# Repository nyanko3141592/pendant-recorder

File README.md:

# pendant-recorder

DTP401525-XE（3.7V・110mAh）を使う、連続録音型のUSB-Cネックレスレコーダーです。現行の4層設計レビューは[確認パッケージ](hardware/xe-minimal/preorder-20261029/release-review-20261029-aligned/START-HERE.txt)に集約しています。現成果物の入口は[初号試作設計](hardware/xe-minimal/preorder-20261029/release-review-20261029-aligned/first-prototype/README.md)です。配線bay・接着ポケット付きケースと同版キットを追加し、C30を同定格在庫品へ変更しました。ファームの購入者向け書込み版と物理性能は未確定です。

**現状は `HOLD` です。注文、支払い、製造データのアップロードは禁止です。** CAD・静的検査・ソフトウェア試験は通過していますが、安全性、16時間連続録音、30時間保存、3 OSでのUSB取込み、ケース強度は実機未確認です。

## 優先順位

今回は低コストで小型の初号試作を作り、実際に使って評価します。基本安全対策を前提に、**使い勝手（特に電池持ち）→小型化→初回費用**の順で判断します。性能は根拠のある理論見積りで達成を見込めれば試作判断へ進め、実測や量産認定を事前条件にしません。室温の明示した仮定では平均3.86mA・約19.9時間（使用可能77mAh）となりますが、SPI電流・動作時間・使用可能容量は未実測です。詳細は[現行要件](docs/requirements.md)を正本とします。

## 現行候補

基板27.5mm角・最大4層・通常through via・固定DTP401525-XE・16時間録音・30時間以上保存が現要件です。旧6層正本とCase V5は履歴として保全し、現候補の製造入力には使用しません。

| 項目 | 現在の確認先 | 判定 |
| --- | --- | --- |
| 回路・4層基板 | [同版KiCad設計](hardware/xe-minimal/preorder-20261029/release-review-20261029-aligned/design/) | 基準PCB b3cdfc064b43…、DRC/未接続/parity 0。電気性能の認定ではない |
| BOM・調達 | [全BOM確認](hardware/xe-minimal/preorder-20261029/release-review-20261029-aligned/live-full-bom-summary.json) | 68実装・36型番。U1/U12/J1通常Pre-order。C30は同定格C501830へ変更し公開実装可能45,731個を確認 |
| 製造資料 | [確認パッケージ](hardware/xe-minimal/preorder-20261029/release-review-20261029-aligned/START-HERE.txt) | Gerber/drill/BOM/CPL同梱。回転・DFM・90Ω・総額は未確定、upload禁止 |
| ケース・実寸ダミー | [現優先候補](hardware/xe-minimal/preorder-20261029/release-review-20261029-aligned/mechanical-first-prototype/ASSEMBLY.md) | 約30.8×37.5×14.2mm。配線通路・蓋接着ポケット、ケース3点＋PCBA/電池ダミーSTEP/STL/3MF。CADとoffline slice確認、現物fit・強度は未認定 |
| ファーム・取込み | [STM32](firmware/stm32/) / [host](host/README.md) | 現codecで暗号化・復号の非実機試験済み。工場imageと3 OS実機動作は未確定 |
| 組立・試験 | [現4層の手順](hardware/xe-minimal/preorder-20261029/release-review-20261029-aligned/ASSEMBLY-AND-EVT.txt) | 発注前の設計確認と試作後の実測を分離。実測合格は主張しない |
| 残件 | [release-gates.json](hardware/xe-minimal/preorder-20261029/release-review-20261029-aligned/release-gates.json) | 部品入庫・注文時DFM/placement・正式USB ID/cutoff/工場format・実物fit/安全/性能評価が残る |

## 製造と購入者作業の境界

JLCPCB Standard PCBAで両面実装、検査、書込み、出荷前パネル分割まで完結させる方針です。購入者による電子部品の調達、部品支給、はんだ、圧着、配線加工は認めません。購入者が用意して組み付けるものは、固定型番のDTP401525-XE、ケース、ネックレス紐だけです。業者完結できない場合は代替部品または設計変更とし、個別問い合わせを前提に進めません。

## 発注を止めている条件

発注前の設計残件は[release-gates.json](hardware/xe-minimal/preorder-20261029/release-review-20261029-aligned/release-gates.json)を参照してください。試作後の安全・16時間録音・30時間保存・USB・ケース強度試験は未実施です。発注前設計確認の完了と実機認定を区別し、注文・支払い・upload・業者連絡・実印刷は禁止のままです。

旧XIAO/ESP32、旧PCB、旧ケース、外付け温度センサー案は比較・履歴資料であり、現行製造データへ混ぜません。

[プロトコル](docs/protocol/README.md) / [貢献手順](CONTRIBUTING.md) / [MITライセンス](LICENSE) / [第三者通知](THIRD_PARTY_NOTICES.md)

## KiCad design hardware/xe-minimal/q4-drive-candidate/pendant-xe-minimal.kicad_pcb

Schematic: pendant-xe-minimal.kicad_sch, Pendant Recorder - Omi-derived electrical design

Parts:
C1, C2, C3, C6, C9, C22, C26: 100n; C_0402_1005Metric
C4: 10u; C_0603_1608Metric
C5: 4.7u; C_0603_1608Metric
C7, C16, C25: 1u; C_0402_1005Metric
C13: 2.2u 10V; C_0402_1005Metric
C14: 2.2u; C_0402_1005Metric
C15: 10u 10V effective >=1u; C_0603_1608Metric
C27: 4.7u effective TBD; C_0603_1608Metric
C28: 10n; C_0402_1005Metric
C29, C32, C33: 100n 10V; C_0402_1005Metric
C30: 50p 50V C0G; C_0402_1005Metric
C31: 1u 10V; C_0402_1005Metric
D6: amber LED 0402 TBD; LED_0402_1005Metric
J1: USB4105-GF-A (candidate); USB_C_GCT_USB4105_GroundLand112
J2: Molex781710003 / DTP401525-XE; Molex_Pico-EZmate_78171-0003_1x03-1MP_P1.20mm_Vertical
J3: Factory SWD pogo candidate; SWD_Pogo_5Pad_P1.27mm
Q3, Q4: DMN63D8L-7; SOT-23
Q5, Q6, Q7: 2N7002; SOT-23
R1: 0R; R_0402_1005Metric
R2: 10k; R_0402_1005Metric
R3, R4, R13, R15, R22: 100k; R_0402_1005Metric
R6, R7: 5.1k 1%; R_0402_1005Metric
R10: 6.8k 1%; R_0402_1005Metric
R11, R39: 20k 1%; R_0402_1005Metric
R12, R36, R37, R38, R40, R45, R46, R49, R50: 100k 1%; R_0402_1005Metric
R14: 1M; R_0402_1005Metric
R21, R23: 22R tentative; R_0402_1005Metric
R24, R25, R28: 47k; R_0402_1005Metric
R32: 6.8k tentative; R_0402_1005Metric
R33, R34: 1M 1%; R_0402_1005Metric
R35, R47, R48: 10k 1%; R_0402_1005Metric
R41: 7.5k 1%; R_0402_1005Metric
R42: 130k 1%; R_0402_1005Metric
R43: 4.7k 1%; R_0402_1005Metric
R44: 390k 1%; R_0402_1005Metric
SW1: B3U-1000P (candidate); SW_SPST_B3U-1000P
TH1: NCP18XH103F03RB 10k 1% B3380 candidate; R_0603_1608Metric
TP1, TP2, TP3, TP5, TP6: TestPoint; TestPoint_Pad_D1.0mm
U1: STM32U535CEU6; QFN-48-1EP_7x7mm_P0.5mm_EP5.6x5.6mm
U2: USBLC6-2P6; SOT-666
U3: BQ25185DLHR; Texas_DLH0010A_WSON-10-1EP_2.2x2mm_P0.4mm_EP0.9x1.5mm
U4: TPS7A0233PDBVR; SOT-23-5
U8: IM69D130V01XTSA1; IM69D130_JLC_SMD_trial
U10: TPS22916CYFPR; TPS22916_YFP4
U11: CSNP32GCR01-BOW candidate; CSNP32GCR01_LGA8
U12: TLV7042DDFR; SOT-23-8
U13: MAX4995CAUT+T; SOT-23-6
U14: SN74HCS74DYYR; Texas_DYY0014A
U15: TLV803EB29DBZR; SOT-23

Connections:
/BAT: C14.1, J2.1 (PACK_PLUS), R33.1, TP1.1, U3.2 (BAT)
/BAT_ADC: C28.1, R33.2, R34.1, U1.11 (PA1)
/BAT_TS: R37.2, TH1.1 (SENSE), U12.2 (INA-), U12.5 (INB+)
/BOOT0: R3.1, U1.44 (PH3)
/BUTTON_N: R4.2, SW1.1, U1.38 (PA15)
/CC1: J1.A5 (CC1), R6.1
/CC2: J1.B5 (CC2), R7.1
/CHARGER_TS: R35.1, U3.6 (TS_MR)
/CHG_ALLOW: R43.1, U1.20 (PB2)
/CHG_GUARD_GATE: Q4.1 (G), R36.1, R43.2, U12.1 (OUTA), U12.7 (OUTB)
/CHG_INHIBIT_GATE: Q4.3 (D), R12.2, U3.4 (CE_N)
/CHG_N: R11.2, U1.27 (PB14), U3.9 (STAT1)
/GND: C1.2, C2.2, C3.2, C4.2, C5.2, C6.2, C7.2, C9.2, C13.2, C14.2, C15.2, C16.2, C22.2, C25.2, C26.2, C27.2, C28.2, C29.2, C30.2, C31.2, C32.2, C33.2, D6.1 (K), J1.A1 (GND), J1.A12 (GND), J1.B1 (GND), J1.B12 (GND), J1.SH (SHIELD), J2.3 (PACK_MINUS), J3.5 (GND), Q3.2 (S), Q4.2 (S), Q5.2 (S), Q6.2 (S), Q7.2 (S), R3.2, R6.2, R7.2, R10.2, R14.2, R22.2, R34.2, R35.2, R36.2, R39.2, R41.2, R42.2, R44.2, R46.2, R49.2, R50.2, SW1.2, TH1.2 (RETURN), TP6.1, U1.8 (VSSA), U1.23 (VSS), U1.35 (VSS), U1.47 (VSS), U1.49 (VSS), U2.2 (GND), U3.5 (GND), U3.11 (EP), U4.2 (GND), U8.4 (SELECT), U8.5 (GND), U10.B1 (GND), U11.4 (VSS), U12.4 (VEE), U13.2 (GND), U14.7 (GND), U14.11 (2CLK), U14.12 (2D), U14.13 (2CLR_N), U15.1 (GND)
/ILIM_VSET: R42.1, U3.7 (ILIM_VSET)
/ISET: C30.1, R10.1, U3.8 (ISET)
/NRST: C9.1, J3.3 (nRESET), R2.2, U1.7 (NRST)
/PDM_CLK: R21.2, U8.3 (CLOCK)
/PDM_CLK_MCU: R21.1, U1.39 (PB3)
/PDM_DATA: U1.40 (PB4), U8.1 (DATA)
/SD_CLK: R23.2, U11.3 (CLK)
/SD_CLK_MCU: R23.1, U1.15 (PA5)
/SD_CS_N: R28.2, U1.14 (PA4), U11.2 (CS_N)
/SD_EN: R22.1, U1.41 (PB5), U10.B2 (ON)
/SD_MISO: R25.2, U1.16 (PA6), U11.6 (DO)
/SD_MOSI: R24.2, U1.17 (PA7), U11.5 (DI)
/SD_V3: C26.1, C27.1, R24.1, R25.1, R28.1, TP5.1, U10.A1 (VOUT), U11.8 (VDD)
/STATUS_LED: R32.1, U1.29 (PA8)
/STATUS_LED_A: D6.2 (A), R32.2
/SWCLK: J3.4 (SWCLK), U1.37 (PA14)
/SWDIO: J3.2 (SWDIO), U1.34 (PA13)
/SYS: C15.1, TP2.1, U3.1 (SYS), U4.1 (IN), U4.3 (EN)
/TS_COLD_REF: R38.2, R39.1, U12.3 (INA+)
/TS_HOT_REF: R40.2, R41.1, U12.6 (INB-)
/USB_DM: J1.A7 (D-), J1.B7 (D-), U1.32 (PA11), U2.3 (IO2), U2.4 (IO2)
/USB_DP: J1.A6 (D+), J1.B6 (D+), U1.33 (PA12), U2.1 (IO1), U2.6 (IO1)
/USB_HIGH_BUDGET: Q5.1 (G), R46.1, U1.42 (PB6)
/USB_HIGH_BUDGET_DRAIN: Q5.3 (D), R45.2
/USB_ILIM_SET: R44.1, R45.1, U13.3 (SETI)
/USB_INPUT_ON: U13.4 (ON), U14.6 (1Q_N)
/USB_LATCH_CLEAR_N: Q7.3 (D), R48.2, U14.1 (1CLR_N), U15.2 (RESET_N)
/USB_LATCH_CLOCK: Q6.3 (D), R47.2, U14.3 (1CLK)
/USB_RESUME_PULSE: Q7.1 (G), R50.1, U1.19 (PB1)
/USB_SUSPEND_PULSE: Q6.1 (G), R49.1, U1.12 (PA2)
/V3V3: C1.1, C2.1, C3.1, C4.1, C16.1, C22.1, C25.1, C29.1, J3.1 (VTref), R1.1, R2.1, R4.1, R11.1, R15.1, R37.1, R38.1, R40.1, TP3.1, U1.1 (VBAT), U1.24 (VDD), U1.36 (VDD), U1.48 (VDD), U4.5 (OUT), U8.2 (VDD), U10.A2 (VIN), U12.8 (VCC)
/VBUS: C31.1, C32.1, C33.1, J1.A4 (VBUS), J1.A9 (VBUS), J1.B4 (VBUS), J1.B9 (VBUS), R13.1, R47.1, R48.1, U2.5 (VBUS), U13.5 (IN), U14.2 (1D), U14.4 (1PRE_N), U14.10 (2PRE_N), U14.14 (VCC), U15.3 (VDD)
/VBUS_GATE: Q3.1 (G), R13.2, R14.1
/VBUS_LIMITED: C13.1, R12.1, U3.10 (IN), U13.1 (OUT)
/VBUS_N: Q3.3 (D), R15.2, U1.10 (PA0)
/VCAP: C5.1, U1.22 (VCAP)
/VDDA: C6.1, C7.1, R1.2, U1.9 (VDDA)

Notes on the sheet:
01 MCU / RTC / UI
02 USB-C / CHARGER
03 POWER / FUEL GAUGE
04 AUDIO / SD / INDICATORS
ENGINEERING DRAFT - NOT FOR FABRICATION - See hardware/xe-minimal/README.md

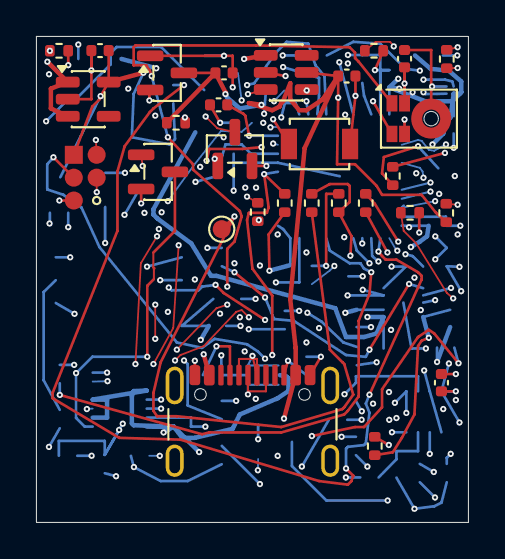
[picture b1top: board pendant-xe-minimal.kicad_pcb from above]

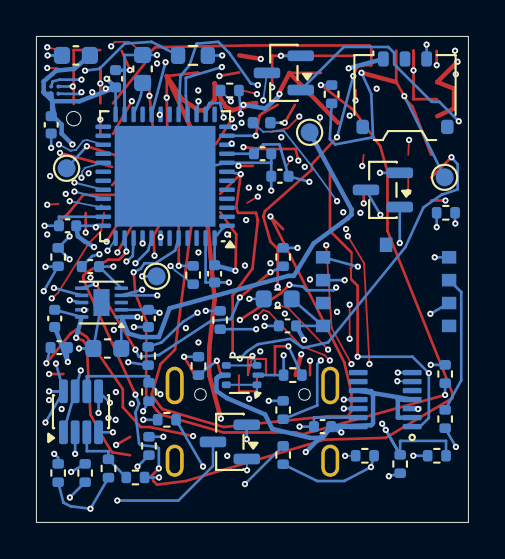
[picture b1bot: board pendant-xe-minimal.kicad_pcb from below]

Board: 6 copper layers, 24.0 x 27.0 mm, 86 parts (57 on the bottom side), 50 nets.

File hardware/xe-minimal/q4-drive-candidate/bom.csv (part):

Reference,Part/value,Footprint,Design note
U1,STM32U535CEU6,Package_DFN_QFN:QFN-48-1EP_7x7mm_P0.5mm_EP5.6x5.6mm,512KB Flash/274KB RAM; non-SMPS UFQFPN48. PB3/PB4 ADF AF3; PA5/6/7 SPI1 AF5. VDD USB shared 3.3V. JLC acceptance and pin review pending.
C1,100n,Capacitor_SMD:C_0402_1005Metric,
C4,10u,Capacitor_SMD:C_0603_1608Metric,Main bulk capacitor; check startup and effective capacitance.
C9,100n,Capacitor_SMD:C_0402_1005Metric,
R2,10k,Resistor_SMD:R_0402_1005Metric,
J3,Factory SWD pogo candidate,PendantMinimal:SWD_Pogo_5Pad_P1.27mm,Five exposed pads; factory fixture required; VTref sense only. No buyer flashing.
SW1,B3U-1000P (candidate),Button_Switch_SMD:SW_SPST_B3U-1000P,
R4,100k,Resistor_SMD:R_0402_1005Metric,
J1,USB4105-GF-A (candidate),PendantD1:USB_C_GCT_USB4105_GroundLand112,Exact footprint and shield pad numbering pending connector selection
R6,5.1k 1%,Resistor_SMD:R_0402_1005Metric,
R7,5.1k 1%,Resistor_SMD:R_0402_1005Metric,
U2,USBLC6-2P6,Package_TO_SOT_SMD:SOT-666,"ST DS4260 same 6-pin function diagram; smaller package, LCSC C15999 catalog; orientation/land pattern final audit pending."
C13,2.2u 10V,Capacitor_SMD:C_0402_1005Metric,
U3,BQ25185DLHR,Package_DFN_QFN:Texas_DLH0010A_WSON-10-1EP_2.2x2mm_P0.4mm_EP0.9x1.5mm,XE candidate4.1V ±0.5% =>4.1205V upper;44.12mA nominal charging. ILIM500 requires host power policy; thermal contact and battery capacity at4.1V unqualified; charge inhibited.
R10,6.8k 1%,Resistor_SMD:R_0402_1005Metric,XE prototype44.12mA nominal;10%IC/1%R screen39.31..49.02mA below110mA pack maximum. Nominal4.41mA termination exceeds manufacturer1.1mA reference; capacity/16h not guaranteed. No charge enable.
R11,20k 1%,Resistor_SMD:R_0402_1005Metric,
C14,2.2u,Capacitor_SMD:C_0402_1005Metric,
J2,Molex781710003 / DTP401525-XE,Connector_Molex:Molex_Pico-EZmate_78171-0003_1x03-1MP_P1.20mm_Vertical,"Pack manufacturer p9:1red+,2NTC,3black-. Header mating-view pad alignment still requires validation. Built-in NTC has no identified R-T curve; pin2 deliberately NC. Independent factory-mountedTH1 contact sensor is mandatory; no user soldering. Reverse polarity protection review pending."
R12,100k 1%,Resistor_SMD:R_0402_1005Metric,100k VBUS pull-up defaults Q2 to charge inhibited; no MCU GPIO connection to5V.
C15,10u 10V effective >=1u,Capacitor_SMD:C_0603_1608Metric,SYS cap per TI; DC-bias capacitance must be qualified.
U4,TPS7A0233PDBVR,Package_TO_SOT_SMD:SOT-23-5,3.3V main rail: 48-pin MCU has no separate USB supply; dropout/capacity measurement required.
C16,1u,Capacitor_SMD:C_0402_1005Metric,
U8,IM69D130V01XTSA1,Pendant:IM69D130_JLC_SMD_trial,"Direct 3.3V PDM, bottom port; no AAD. 0.768MHz/decimation48 candidate for 16kHz; acoustic validation required."
R21,22R tentative,Resistor_SMD:R_0402_1005Metric,
C22,100n,Capacitor_SMD:C_0402_1005Metric,
U10,TPS22916CYFPR,Pendant:TPS22916_YFP4,Omi SD switch; power-off sequence must tristate ALL SD signals
R22,100k,Resistor_SMD:R_0402_1005Metric,
C25,1u,Capacitor_SMD:C_0402_1005Metric,
R23,22R tentative,Resistor_SMD:R_0402_1005Metric,
R24,47k,Resistor_SMD:R_0402_1005Metric,
R25,47k,Resistor_SMD:R_0402_1005Metric,
R28,47k,Resistor_SMD:R_0402_1005Metric,
C26,100n,Capacitor_SMD:C_0402_1005Metric,
C27,4.7u effective TBD,Capacitor_SMD:C_0603_1608Metric,
TP1,TestPoint,TestPoint:TestPoint_Pad_D1.0mm,
TP2,TestPoint,TestPoint:TestPoint_Pad_D1.0mm,
TP3,TestPoint,TestPoint:TestPoint_Pad_D1.0mm,
TP5,TestPoint,TestPoint:TestPoint_Pad_D1.0mm,
TP6,TestPoint,TestPoint:TestPoint_Pad_D1.0mm,
R32,6.8k tentative,Resistor_SMD:R_0402_1005Metric,"LED current target 0.1-0.2mA; verify LED Vf, daylight readability and GPIO limits"
D6,amber LED 0402 TBD,LED_SMD:LED_0402_1005Metric,"Single status/battery indicator; firmware blinks on demand, normally dark."
C2,100n,Capacitor_SMD:C_0402_1005Metric,
C3,100n,Capacitor_SMD:C_0402_1005Metric,
C5,4.7u,Capacitor_SMD:C_0603_1608Metric,
C6,100n,Capacitor_SMD:C_0402_1005Metric,
C7,1u,Capacitor_SMD:C_0402_1005Metric,
R1,0R,Resistor_SMD:R_0402_1005Metric,
R3,100k,Resistor_SMD:R_0402_1005Metric,
Q3,DMN63D8L-7,Package_TO_SOT_SMD:SOT-23,
R13,100k,Resistor_SMD:R_0402_1005Metric,
R14,1M,Resistor_SMD:R_0402_1005Metric,
R15,100k,Resistor_SMD:R_0402_1005Metric,
R33,1M 1%,Resistor_SMD:R_0402_1005Metric,"Battery divider 1:2; sample after settling, calibrate with VREFINT; not coulomb counting."
R34,1M 1%,Resistor_SMD:R_0402_1005Metric,"Battery divider 1:2; sample after settling, calibrate with VREFINT; not coulomb counting."
C28,10n,Capacitor_SMD:C_0402_1005Metric,"Battery divider 1:2; sample after settling, calibrate with VREFINT; not coulomb counting."
R35,10k 1%,Resistor_SMD:R_0402_1005Metric,Holds normal TS level when released; no floating TS/TTDM in intended circuit.
R36,100k 1%,Resistor_SMD:R_0402_1005Metric,MCU reset/high-Z defaults to no charging permission.
R37,100k 1%,Resistor_SMD:R_0402_1005Metric,Reduce thermistor excitation; 5.25V and99k gives52.99uA maximum branch current and69.60uW maximum thermistor power. Only powered from USB. Shared MCU rail for USB-independent temperature guard; BOR4 and startup timing qualification required.
R38,100k 1%,Resistor_SMD:R_0402_1005Metric, Shared MCU rail for USB-independent temperature guard; BOR4 and startup timing qualification required.
R39,20k 1%,Resistor_SMD:R_0402_1005Metric,Cold threshold candidate. Beta-model sensitivity is not full manufacturer R-T qualification. See temperature-screen.json.
R40,100k 1%,Resistor_SMD:R_0402_1005Metric, Shared MCU rail for USB-independent temperature guard; BOR4 and startup timing qualification required.
R41,7.5k 1%,Resistor_SMD:R_0402_1005Metric,Hot threshold candidate. Reserve margin for contact sensor lag; physical thermal qualification required.
U12,TLV7042DDFR,Package_TO_SOT_SMD:SOT-23-8,"Open-drain wired-AND temperature permission. Either fault pulls Q4 gate low. Board NTC replaces undocumented pack NTC; exact R-T, common-mode error and thermal contact not qualified. Shared MCU rail for USB-independent temperature guard; BOR4 and startup timing qualification required."
Q4,DMN63D8L-7,Package_TO_SOT_SMD:SOT-23,"Pulls BQ25185 CE_N low only when MCU and wired-AND comparator outputs permit. R36 defaults gate low. Startup, leakage and gate-voltage behavior need review."
C29,100n 10V,Capacitor_SMD:C_0402_1005Metric,Place adjacent to U12 supply pins. Shared MCU rail for USB-independent temperature guard; BOR4 and startup timing qualification required.
R42,130k 1%,Resistor_SMD:R_0402_1005Metric,BQ25185 Table6-1:4.1V / ILIM500. Input450/475/498mA. Requires USB preconfiguration/suspend power management; charge stays disabled pending qualification.
C30,50p 50V C0G,Capacitor_SMD:C_0402_1005Metric,BQ25185 SLUSF65B6.1.1.4 low-current <50mA recommendation; final transient behavior requires hardware test.
R43,4.7k 1%,Resistor_SMD:R_0402_1005Metric,MCU permission series resistor; limits current into comparator fault clamp.
TH1,NCP18XH103F03RB 10k 1% B3380 candidate,Resistor_SMD:R_0603_1608Metric,Independent factory-mounted contactNTC required because pack NTC exactR-T unspecified. Electrically insulated compliant contact to pouch and retention must be engineered and tested; no ambient-only charging approval.
U13,MAX4995CAUT+T,Package_TO_SOT_SMD:SOT-23-6,Continuous input limiter; DC screen3.3V only; FLAG explicitlyNC. Not charging qualification.
U14,SN74HCS74DYYR,Pendant_Input:Texas_DYY0014A,RawVBUS retainedOFF latch; Schmitt inputs. POR/resume clearQ=0 =>Q_N enables input. Suspend clocksD=1 =>Q_N disables. UnusedFF heldclear; PRE alwayshigh.
U15,TLV803EB29DBZR,Package_TO_SOT_SMD:SOT-23,"2.93V supervisor;B40us nominal/80us maxunderdatasheetcondition. StandardDBZ pinout, NOT RDBZ or VDBZ. Initializes latch before chargerUVLO; analog startup still needs validation."
R44,390k 1%,Resistor_SMD:R_0402_1005Metric,Input control candidate; tolerance/assembly/physical layout pending
R45,100k 1%,Resistor_SMD:R_0402_1005Metric,Input control candidate; tolerance/assembly/physical layout pending
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
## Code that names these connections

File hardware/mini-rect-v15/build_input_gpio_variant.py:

"""Preserve prior PA2/PA3/PB1 candidate; try accessible PB5/PB6/PB7 pins."""
from pathlib import Path
import json,shutil,subprocess
import wx
app=wx.App(False)
import pcbnew as k
P=Path(__file__).resolve().parent;S=P/'input-control';O=P/'input-control-gpio';O.mkdir(exist_ok=True)
out=O/'input-gpio-source.kicad_pcb';assert not out.exists(),'Preserve existing variant'
for ext in ['.kicad_pro','.kicad_dru']:shutil.copyfile(S/('input-connected-candidate'+ext),out.with_suffix(ext))
b=k.LoadBoard(str(S/'input-connected-candidate.kicad_pcb'));f=next(f for f in b.GetFootprints() if f.GetReference()=='U1');pads={p.GetNumber():p for p in f.Pads() if p.GetNumber()}
d=json.loads((S/'design.json').read_text());u=next(p for p in d['parts'] if p['ref']=='U1');pins={p['number']:p for p in u['pins']}
for old,new,expected in [('12','41','PB5'),('13','42','PB6'),('19','43','PB7')]:
 assert pins[new]['name']==expected and pins[new]['net'] is None
 net=pins[old]['net'];assert net.startswith('USB_');pins[new]['net']=net;pins[old]['net']=None;pads[new].SetNet(b.FindNet('/'+net));pads[old].SetNetCode(0)
d['revision']='mini-rect-v15 input-control PB5/PB6/PB7 candidate NOT RELEASED';(O/'design.json').write_text(json.dumps(d,indent=2)+'\n')
shutil.copytree(S/'Pendant_Input.pretty',O/'Pendant_Input.pretty',dirs_exist_ok=True);shutil.copyfile(S/'fp-lib-table',O/'fp-lib-table');shutil.copyfile(S/'pendant-mini-rect-v15.kicad_pro',O/'pendant-mini-rect-v15.kicad_pro')
subprocess.run(['python3',str(P/'generate_schematic.py'),'mini-rect-v15',str(O)],check=True)
k.ZONE_FILLER(b).Fill(b.Zones());k.SaveBoard(str(out),b)
for name in ['check_board_parity.py','check_usb_preserved.py']:shutil.copyfile(S/name,O/name)
s=(S/'connect_remaining.py').read_text().replace('input-route-neck','input-gpio-source')
s=s.replace("  print(results[-1],flush=True)","  print(results[-1],flush=True)\n  if not accepted:\n   tag=name.strip('/');(P/('rejected-'+tag+'.json')).write_text(json.dumps(check,indent=2)+'\\n');k.SaveBoard(str(P/('rejected-'+tag+'.kicad_pcb')),b)")
(O/'connect_remaining.py').write_text(s)
print('GPIO variant created without changing old candidate or firmware yet')

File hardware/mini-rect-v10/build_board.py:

#!/usr/bin/env python3
"""Build an electrically netted, unrouted review board. Never a fabrication release."""
import json,csv,uuid
from pathlib import Path
import wx
app=wx.App(False)
import pcbnew as pcb
ROOT=Path(__file__).resolve().parents[2];OUT=ROOT/'hardware/mini-rect-v10'
SYS=Path('/Applications/KiCad/KiCad.app/Contents/SharedSupport/footprints')
data=json.loads((OUT/'design.json').read_text());parts=data['parts']
mm=pcb.FromMM
def pt(x,y):return pcb.VECTOR2I(mm(x),mm(y))
board=pcb.BOARD();board.SetCopperLayerCount(4);board.GetDesignSettings().SetBoardThickness(mm(.8))
nets={}
for name in sorted({q['net'] for p in parts for q in p['pins'] if q['net']}):
 n=pcb.NETINFO_ITEM(board,name);board.Add(n);nets[name]=n
fps={}; dims={};errors=[]
for p in parts:
 lib,name=p['footprint'].split(':');path=OUT/(lib+'.pretty') if lib in ('Pendant','PendantD1') else SYS/(lib+'.pretty')
 f=pcb.FootprintLoad(str(path),name)
 if not f:raise ValueError('Missing '+p['footprint'])
 f.SetFPID(pcb.LIB_ID(lib,name));f.SetReference(p['ref']);f.SetValue(p['value']);f.SetPath(pcb.KIID_PATH('/'+str(uuid.uuid5(uuid.NAMESPACE_URL,'pendant-recorder/mini-rect-v10/root'))+'/'+str(uuid.uuid5(uuid.NAMESPACE_URL,'pendant-recorder/mini-rect-v10/'+p['ref']))))
 f.Reference().SetVisible(False);f.Value().SetVisible(False)
 expected={q['number']:q for q in p['pins']};found=set()
 for pad in f.Pads():
  num=pad.GetNumber()
  if not num or (p['ref']=='J2' and num=='MP'):continue
  if num not in expected:errors.append(p['ref']+': unexpected pad '+num);continue
  found.add(num);net=expected[num]['net']
  if net:pad.SetNet(nets[net])
  else:
   ncname='unconnected-('+p['ref']+'-'+expected[num]['name'].replace(' ','_')+'-Pad'+num+')';nc=pcb.NETINFO_ITEM(board,ncname);board.Add(nc);pad.SetNet(nc)
 for num in expected.keys()-found:errors.append(p['ref']+': missing pad '+num)
 board.Add(f);fps[p['ref']]=f
 bb=f.GetBoundingBox(False,False);dims[p['ref']]=(pcb.ToMM(bb.GetX()),pcb.ToMM(bb.GetY()),pcb.ToMM(bb.GetWidth()),pcb.ToMM(bb.GetHeight()))
if errors:raise ValueError('\n'.join(errors))


import math

def bb(f):
 q=f.GetBoundingBox(False,False);return [pcb.ToMM(q.GetX()),pcb.ToMM(q.GetY()),pcb.ToMM(q.GetWidth()),pcb.ToMM(q.GetHeight())]
def move_center(f,x,y):
 a,b,w,h=bb(f);f.Move(pt(x-a-w/2,y-b-h/2))
def overlaps(a,b,gap=.12):return not(a[0]+a[2]+gap<=b[0] or b[0]+b[2]+gap<=a[0] or a[1]+a[3]+gap<=b[1] or b[1]+b[3]+gap<=a[1])
def inside(x,y,margin=.20):
 # 21 x 23 mm rounded rectangle, R2.5.
 qx=abs(x-10.5)-8;qy=abs(y-11.5)-9
 return math.hypot(max(qx,0),max(qy,0))+min(max(qx,qy),0)<=2.5-margin
occ={'F':[],'B':[]};placed={}
heights={r:(3.56 if r=='J1' else 1.6 if r=='SW1' else 1.4 if r=='J2' else .05 if r=='J3' or r.startswith('TP') else .85 if r=='U11' else 1.3 if r=='U8' else 1.5 if r=='U4' else 1.2 if r in ['U1','U12','Q3','Q4','Q5','Q6'] else .8 if r=='U3' else .6) for r in fps}
# Underside features under the pack may be <=0.85mm, leaving >=0.25mm nominal gap.
pack=[2.75,1.75,15.5,17.5]
def orient(f,side,rot):
 if f.IsFlipped()!=(side=='B'):f.Flip(f.GetPosition(),False)
 f.SetOrientationDegrees(rot)
def allowed(ref,side,q):
 x,y,w,h=q
 if ref!='J1' and not all(inside(a,b) for a in [x,x+w] for b in [y,y+h]):return False
 if any(overlaps(q,b) for b in occ[side]):return False
 if side=='B' and heights[ref]>.85 and overlaps(q,pack,.1):return False
 return True
def put(ref,x,y,side='F',rot=0,force=False):
 f=fps[ref];orient(f,side,rot);move_center(f,x,y);q=bb(f)
 if not force and not allowed(ref,side,q):raise ValueError('fixed does not fit '+ref+str(q))
 occ[side].append(q);placed[ref]=q
 # Through-holes require clearance on opposite face. USB shell only reserve actual holes.
 if ref in ['J3','U8']:
  for pad in f.Pads():
   if pad.GetDrillSize().x:
    x,y=pcb.ToMM(pad.GetPosition().x),pcb.ToMM(pad.GetPosition().y);rr=pcb.ToMM(pad.GetDrillSize().x)/2+.25;occ['B' if side=='F' else 'F'].append([x-rr,y-rr,2*rr,2*rr])
 if ref=='J1':
  for pad in f.Pads():
   if pad.GetDrillSize().x:
    x,y=pcb.ToMM(pad.GetPosition().x),pcb.ToMM(pad.GetPosition().y);occ['B'].append([x-.7,y-1,.0+1.4,2])
put('J1',10.5,18.7)
put('U1',11.75,9.9,'F',180)
put('U11',10.5,10.2,'B',0)
put('J2',4.5,7.2,'F',90)
put('J3',12,3.5,'F',0)
put('U8',18.4,11.5,'F',0)
# Acoustic hole at right edge, outside battery footprint.
targets={'U2':(18.8,18),'U3':(5,17),'U4':(4.3,14),'U12':(18,6.8),'SW1':(18.5,8.5),'D6':(16.8,4),'Y1':(8,14),'Q3':(19,19),'Q4':(7,18),'Q5':(4,18),'Q6':(5,21),'U10':(13,18)}
cap_targets={'C1':('U1','24'),'C2':('U1','36'),'C3':('U1','48'),'C5':('U1','22'),'C6':('U1','9'),'C7':('U1','9'),'C9':('U1','7'),'C11':('Y1','1'),'C12':('Y1','2'),'C16':('U4','5'),'C15':('U3','1'),'C22':('U8','2'),'C25':('U10','A2'),'C26':('U11','8'),'C27':('U11','8'),'C29':('U12','8'),'C13':('U3','10'),'C14':('U3','2'),'C30':('U3','8')}
remaining=sorted((r for r in fps if r not in placed),key=lambda r:(0 if r in targets else 1 if r in cap_targets else 2,-dims[r][2]*dims[r][3]))
for ref in remaining:
 f=fps[ref];best=None;tx,ty=targets.get(ref,(12,13))
 # Prefer capacitor local to attached IC supply pad; enforce pin proximity later in review.
 if ref not in targets:
  pn=next(p for p in parts if p['ref']==ref);ns={p['net'] for p in pn['pins'] if p['net'] not in [None,'GND','V3V3','SYS','BAT','VBUS']}
  peers=[p for r in placed for p in fps[r].Pads() if p.GetNetname() in ns]
  if peers:tx=sum(pcb.ToMM(p.GetPosition().x) for p in peers)/len(peers);ty=sum(pcb.ToMM(p.GetPosition().y) for p in peers)/len(peers)
 preferred='F'
 if ref in cap_targets:
  pr,pn=cap_targets[ref];parent=fps[pr];pad=next(p for p in parent.Pads() if p.GetNumber()==pn);tx,ty=pcb.ToMM(pad.GetPosition().x),pcb.ToMM(pad.GetPosition().y);preferred='B' if parent.IsFlipped() else 'F'
 for side in ['F','B']:
  for rot in [0,90]:
   orient(f,side,rot);_,_,w,h=bb(f)
   for iy in range(2,97):
    y=iy*.25
    for ix in range(2,95):
     x=ix*.25;q=[x-w/2,y-h/2,w,h]
     if not allowed(ref,side,q):continue
     score=(x-tx)**2+(y-ty)**2+(0 if side==preferred else 4)
     if best is None or score<best[0]:best=(score,x,y,side,rot)
 if not best:raise ValueError('No placement '+ref)
 _,x,y,side,rot=best;put(ref,x,y,side,rot);print(ref,x,y,side,flush=True)
# Rounded rectangular outline sampled at one degree. No routing implied.
outline=[]
for cx,cy,start in [(18.5,2.5,-90),(18.5,20.5,0),(2.5,20.5,90),(2.5,2.5,180)]:
 for i in range(91):
  a=math.radians(start+i);outline.append((cx+2.5*math.cos(a),cy+2.5*math.sin(a)))
# Close the perimeter.
for a,b in zip(outline,outline[1:]+outline[:1]):
 line=pcb.PCB_SHAPE();line.SetShape(pcb.SHAPE_T_SEGMENT);line.SetStart(pt(*a));line.SetEnd(pt(*b));line.SetLayer(pcb.Edge_Cuts);line.SetWidth(mm(.05));board.Add(line)
# Avoid inappropriate persistent default manufacturing settings; restore project after process exits.
for n in nets.values():n.SetNetname('/'+n.GetNetname())
board.BuildListOfNets();pcb.SaveBoard(str(OUT/'pendant-mini-rect-v10.kicad_pcb'),board)
report=[]
for r,f in fps.items():
 x,y,w,h=bb(f);report.append(dict(ref=r,x=round(x+w/2,5),y=round(y+h/2,5),w=round(w,5),h=round(h,5),side='B' if f.IsFlipped() else 'F',rotation=f.GetOrientationDegrees(),height=heights[r]))
(OUT/'placement.json').write_text(json.dumps(report,indent=2))
(OUT/'outline.json').write_text(json.dumps(outline))
mic=[p for p in fps['U8'].Pads() if p.GetDrillSize().x][0]
(OUT/'mic-port.json').write_text(json.dumps([dict(x=pcb.ToMM(mic.GetPosition().x),y=pcb.ToMM(mic.GetPosition().y),diameter=.8)]))
print('placed',len(report),'tracks',len(board.GetTracks()))
